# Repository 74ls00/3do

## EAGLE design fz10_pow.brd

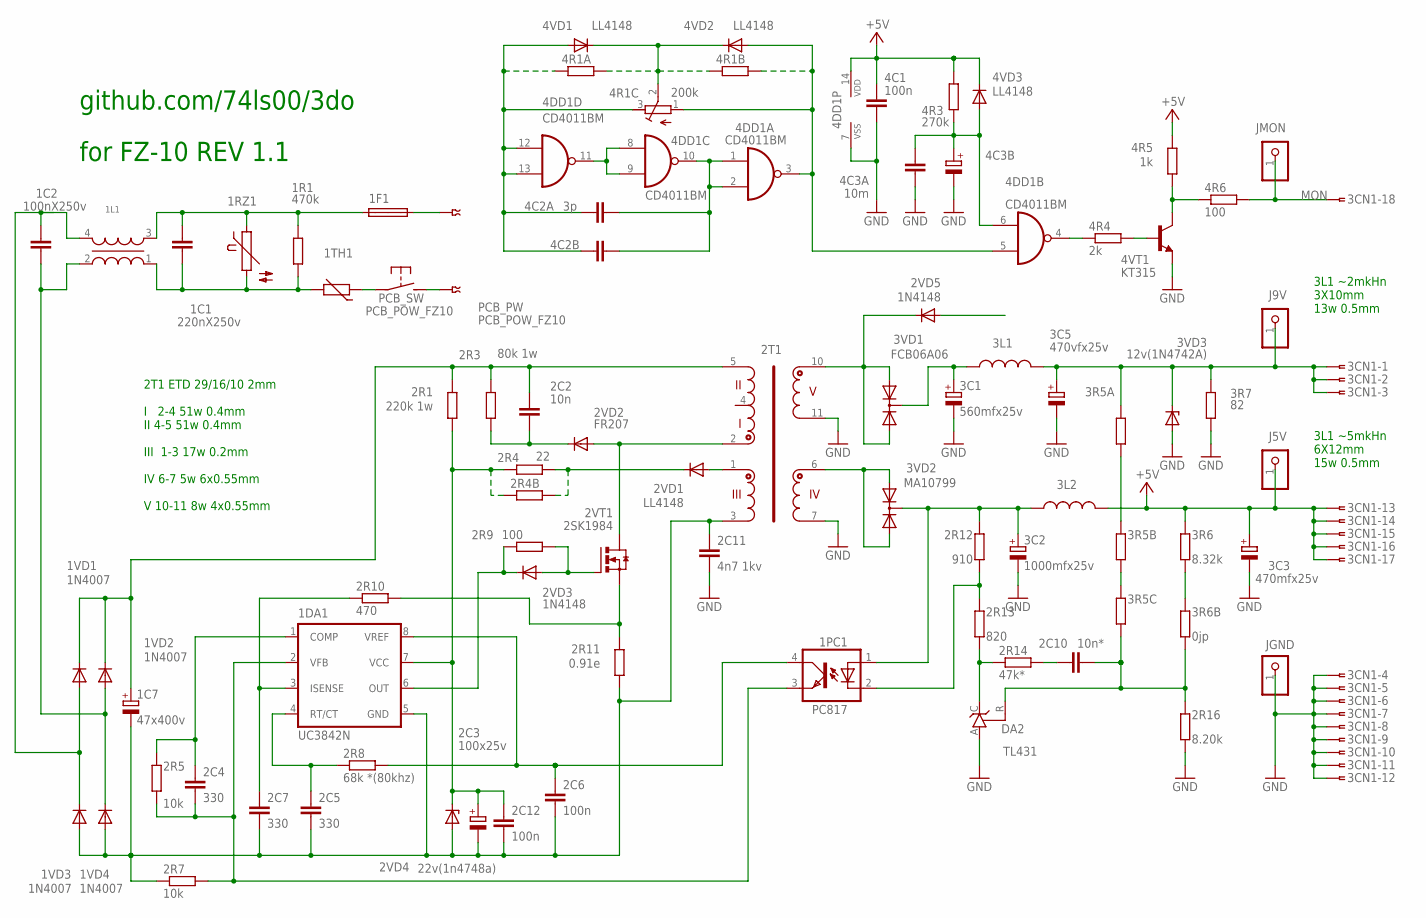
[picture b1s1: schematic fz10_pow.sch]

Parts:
1C1: 220nX250v; C_26X9
1C2: 100nX250v; C150-084X183
1C7: 47x400v; EB22,5D
1DA1: UC3842N; DIL08
1F1: SHK20L
1L1: LFLF-10X13; LF-10X13
1PC1: PC817; DIL04
1R1: 470k; 0309/12
1RZ1: S1210
1TH1: THERMISTOR-7,5; R-7,5
1VD1, 1VD2, 1VD3, 1VD4: 1N4007; DO41-10
2C2: 10n; C075-032X103
2C3: 100x25v; E2,5-6
2C4, 2C5, 2C7: 330; C050-025X075
2C6, 2C12, 4C1: 100n; C0805
2C10: 10n*; C050-025X075
2C11: 4n7 1kv; C075-032X103
2R1: 220k 1w; P0613/15
2R3: 80k 1w; P0613/15
2R4: 22; M0805
2R4B, 3R5C: R-EU_0207/10; 0207/10
2R5: 10k; M0805
2R7: 10k; R0805
2R8: 68k *(80khz); R0805
2R9: 100; 0204/7
2R10: 470; 0207/10
2R11: 0.91e; P0613/15
2R12: 910; R1206
2R13: 820; 0207/10
2R14: 47k*; R1206
2R16: 8.20k; R1206
2T1: TRANS_ER29; ER29
2VD1, 4VD1, 4VD2, 4VD3: LL4148; SOD80C
2VD2: FR207; DO35-10
2VD3, 2VD5: 1N4148; DO35-7
2VD4: 22v(1n4748a); DO35Z10
2VT1: 2SK1984; TO262-V
3C1: 560mfx25v; E5-10,5
3C2: 1000mfx25v; E5-13
3C3: 470mfx25v; E5-8,5
3C5: 470vfx25v; E5-8,5
3CN1: FTOP-18
3L1, 3L2: L-USTFI0305; TFI0305
3R5A, 3R5B: R-EU_M1206; M1206
3R6: 8.32k; 0204/7
3R6B: 0jp; 0204/7
3R7: 82; P0613/15
3VD1: FCB06A06; TO220ABS
3VD2: MA10799; TO220ABS
3VD3: 12v(1N4742A); DO34Z7
4C2A: 3p; C050-025X075
4C2B: C-EUC1206; C1206
4C3A: 10m; C1812
4C3B: CPOL-EUE2.5-5; E2,5-5
4DD1: CD4011BM; SO14
4R1A, 4R1B: R-EU_R1206; R1206
4R1C: 200k; RTRIM3296W
4R3: 270k; R1206
4R4: 2k; R1206
4R5: 1k; R1206
4R6: 100; R1206
4VT1: KT315; TO92-ECB
DA2: TL431; TO92-CLP
J5V, J9V: PINHD-1X1; 1X01
JGND: PINHD-1X1; 1X01
JMON: PINHD-1X1; 1X01
PCB: PCB_POW_FZ10; POW_FZ10

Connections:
+5V: 3C3.+, 3CN1.13, 3CN1.14, 3CN1.15, 3CN1.16, 3CN1.17, 3L2.2, 3R6.2, 4C1.1, 4DD1.14 (VDD), 4R3.2, 4R5.2, 4VD3.C, J5V.1
+16IN: 1DA1.7 (VCC), 2C3.+, 2C12.1, 2R1.1, 2R4.1, 2R4B.1, 2VD4.C
-IN: 1C7.-, 1DA1.5 (GND), 1VD3.A, 1VD4.A, 2C3.-, 2C5.2, 2C6.2, 2C7.2, 2C11.1, 2C12.2, 2R7.1, 2R11.1, 2T1.3 (OP2), 2VD4.A
GND: 2C11.2, 2R16.1, 2T1.7 (O2.2), 2T1.11 (9V2), 3C1.-, 3C2.-, 3C3.-, 3C5.-, 3CN1.4, 3CN1.5, 3CN1.6, 3CN1.7, 3CN1.8, 3CN1.9, 3CN1.10, 3CN1.11, 3CN1.12, 3R7.1, 3VD3.A, 4C1.2, 4C3A.2, 4C3B.-, 4DD1.7 (VSS), 4VT1.E, DA2.A, JGND.1
MON: 3CN1.18, 4R6.2, JMON.1
unnamed: 4C2A.2, 4C2B.2, 4DD1.12 (I0), 4DD1.13 (I1), 4R1A.1, 4R1C.3 (E), 4VD1.A
unnamed: 4DD1.8 (I0), 4DD1.9 (I1), 4DD1.11 (O)
unnamed: 1DA1.4 (RT/CT), 2C5.1, 2R8.1
unnamed: 1DA1.3 (ISENSE), 2C7.1, 2R10.1
unnamed: 2T1.10 (9V1), 2VD5.C, 3VD1.A1, 3VD1.A2
unnamed: 1DA1.1 (COMP), 2C4.1, 2R5.2
unnamed: 4DD1.3 (O), 4DD1.5 (I0), 4R1B.2, 4R1C.1 (A), 4VD2.A
unnamed: 1DA1.6 (OUT), 2R9.1, 2VD3.C
unnamed: 1TH1.1, PCB.SW1
unnamed: 4R1A.2, 4R1B.1, 4R1C.2 (S), 4VD1.C, 4VD2.C
unnamed: 2R9.2, 2VD3.A, 2VT1.1 (G)
unnamed: 1PC1.2 (C), 2R12.1, 2R13.2
unnamed: 1PC1.1 (A), 2R12.2, 3C2.+, 3L2.1, 3VD2.C
unnamed: 2R13.1, 2R14.1, DA2.C
unnamed: 1C2.1, 1L1.4, 1VD1.A, 1VD3.C
unnamed: 2C10.2, 2R14.2
unnamed: 2T1.2 (IN2), 2VD2.A, 2VT1.2 (D)
unnamed: 1F1.1A, PCB.POW2 (2)
unnamed: 4C2A.1, 4C2B.1, 4DD1.1 (I0), 4DD1.2 (I1), 4DD1.10 (O)
unnamed: 1DA1.8 (VREF), 1PC1.4 (COL), 2C6.1, 2R8.2
unnamed: 2R10.2, 2R11.2, 2VT1.3 (S)
unnamed: 2R4.2, 2R4B.2, 2VD1.C
unnamed: 1C7.+, 1VD1.C, 1VD2.C, 2C2.1, 2R1.2, 2R3.2, 2T1.5 (IN1)
unnamed: 2T1.1 (OP1), 2VD1.A
unnamed: 4DD1.4 (O), 4R4.1
unnamed: 4R4.2, 4VT1.B
unnamed: 3R5A.1, 3R5B.2
unnamed: 2T1.6 (O2.1), 3VD2.A1, 3VD2.A2
unnamed: 4R5.1, 4R6.1, 4VT1.C
unnamed: 2C2.2, 2R3.1, 2VD2.C
unnamed: 1C1.2, 1L1.1, 1R1.1, 1RZ1.2, 1TH1.2
unnamed: 1C1.1, 1F1.2A, 1L1.3, 1R1.2, 1RZ1.1
unnamed: PCB.POW1 (1), PCB.SW2 (S)
unnamed: 4C3A.1, 4C3B.+, 4DD1.6 (I1), 4R3.1, 4VD3.A
unnamed: 3C5.+, 3CN1.1, 3CN1.2, 3CN1.3, 3L1.2, 3R5A.2, 3R7.2, 3VD3.C, J9V.1
unnamed: 3C1.+, 3L1.1, 3VD1.C
unnamed: 1DA1.2 (VFB), 1PC1.3 (EMIT), 2C4.2, 2R5.1, 2R7.2
unnamed: 3R5B.1, 3R5C.2
unnamed: 2C10.1, 2R16.2, 3R5C.1, 3R6B.1, DA2.R
unnamed: 3R6.1, 3R6B.2
unnamed: 1C2.2, 1L1.2, 1VD2.A, 1VD4.C

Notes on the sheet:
github.com/74ls00/3do
for FZ-10 REV 1.1
2T1 ETD 29/16/10 2mm I 2-4 51w 0.4mm II 4-5 51w 0.4mm III 1-3 17w 0.2mm IV 6-7 5w 6x0.55mm V 10-11 8w 4x0.55mm
3L1 ~2mkHn 3X10mm 13w 0.5mm
3L1 ~5mkHn 6X12mm 15w 0.5mm

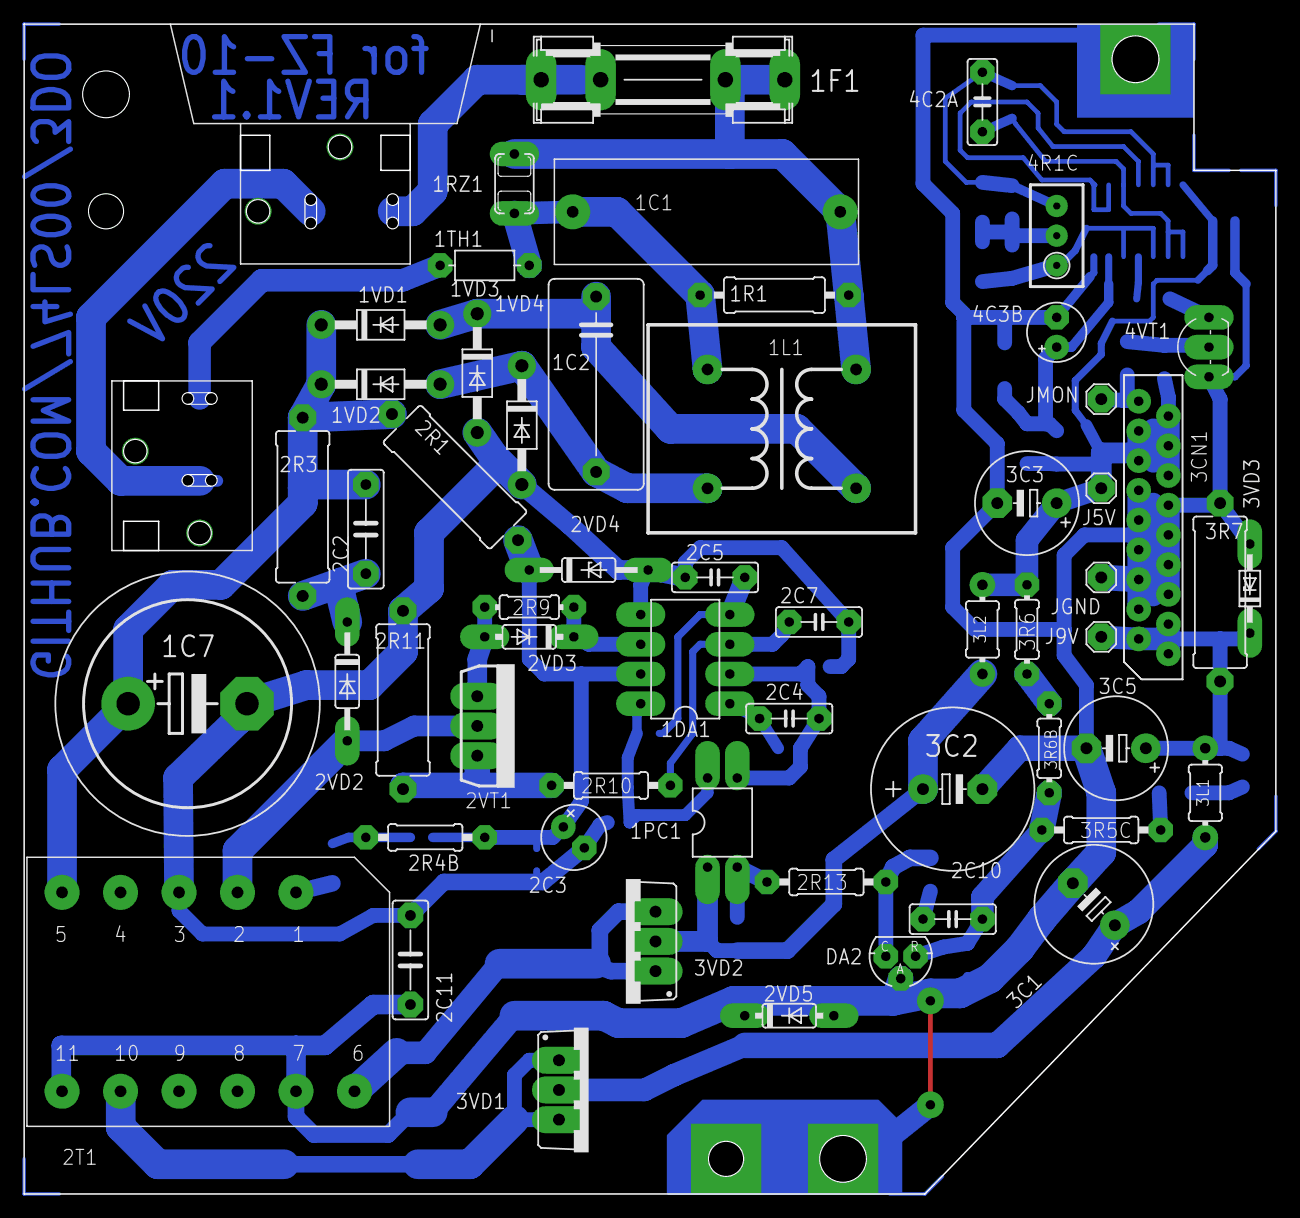
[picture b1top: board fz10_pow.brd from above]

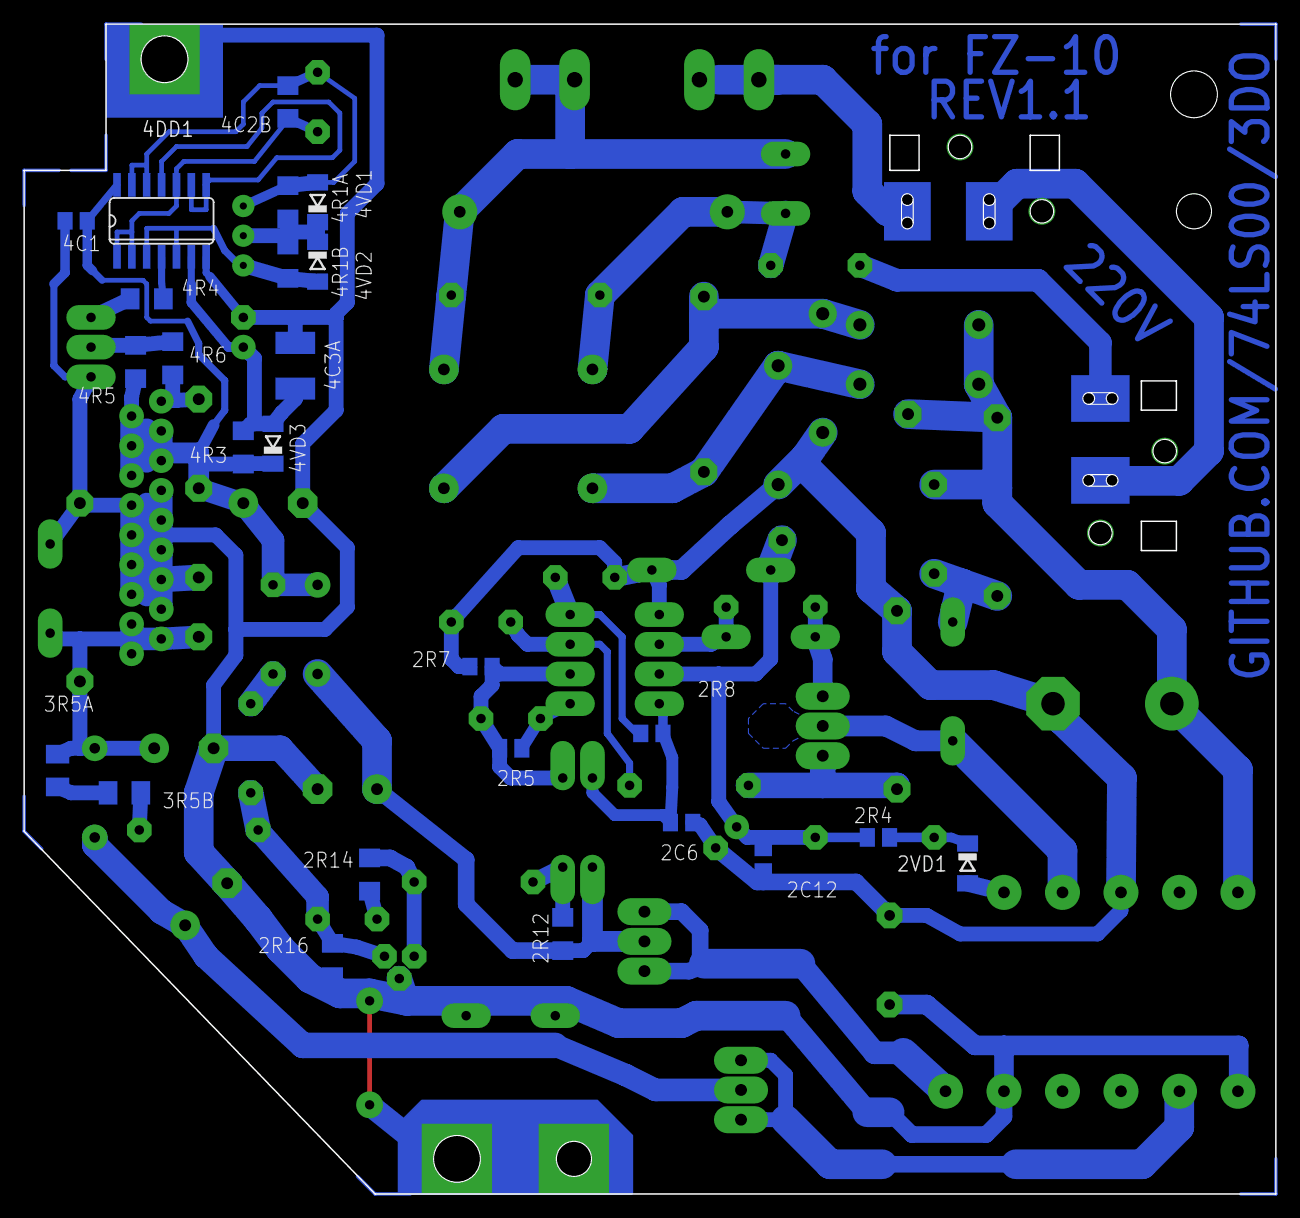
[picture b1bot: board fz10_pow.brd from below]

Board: 2 copper layers, 107.0 x 100.0 mm, 83 parts (25 on the bottom side), 46 nets.

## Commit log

2017-03-22 r1.0
